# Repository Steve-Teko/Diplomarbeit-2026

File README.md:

# Diplomarbeit-2026
Offizielle Repository fuer die Diplomarbeit von Steve

**Idee:**
Die Idee ist es Leiterplatten zu designen, die in einem neuen oder bestehenden SmartHome mit einfachen Schritten integrierbar sind.
Es sollen einfache aber Funktionsreiche Leiterplatten die z.B. im Fall des Aktor Prints, per I2C an bereits vorhandene Steuerungen verwendet werden koennen.

**Meine Qualifikationen:**
Gelernt habe ich Automatiker und interessiere mich seit meiner Kindheit fuer viele Technik relevante Themen. Schulisch war ich schon immer einer dem die Themen Kunst und Sprachen weniger interessierten im vergleich zu Mathe, Physik und Handarbeit.
Mit 23 hatte ich eine Entscheidung getroffen, mich Schulisch weiterzubilden. Dies ist bis jetzt immer noch eine Entscheidung die ich nicht bereue. Der Weg bis zu dieser Arbeit war steinig und hart.
Leiterplatten hatte ich einmal in der Lehre mit meinem damaligen Lehrlingsbetreuer gezeichnet, dies aber danach nie mehr ausgefuehrt. Damals hatten wir Eagle als Programm.

**Die Umsetzung:**
Zu diesem Repo existiert noch meine Arbeit die ich Paralell dazu Schreibe. Die Idee des Repo ist es die notwendigen Daten: KiCad, Gerber Files, Gehause oder Programmzeilen fuer spaetere vorhaben zu Speichern.
Die Arbeit werde ich nicht auf das Repo hochladen.

**Haftungsausschluss:**
Ich bin weder fuer die korrekte Anwendung noch meine Fehler Verantwortlich, saemtliche Schaeden die durch alle Dateien auf diesem Repo verursacht wurden, sind alleinig dem Anwender zuzuschreiben.
Die Leiterplatten sind von keinem Pruefunternehmen abgenommen oder auf ihre Sicherheit geprueft worden. Bei Verwendung sind alle Regeln der Technik zu beachten.

#################################################################################################

Official repository for Steve's diploma thesis.

**Idea**
The concept is to design printed circuit boards (PCBs) that can be easily integrated into a new or existing smart home system.
The goal is to create simple yet feature-rich PCBs—such as the actuator board—that can connect to existing control systems via I2C.

**My Qualifications**
I am a trained automation technician (Automatiker) and have been interested in various tech-related topics since childhood. At school, I was always far less interested in art and languages compared to math, physics, and practical crafts.
At age 23, I decided to further my education—a choice I still do not regret. The path leading up to this project has been tough and challenging.
I had designed PCBs once during my apprenticeship alongside my mentor using EAGLE, but I never worked with PCB design again after that.

**Implementation**
In addition to this repository, I am writing my written thesis in parallel. The purpose of this repo is to store the necessary project files—such as KiCad files, Gerber files, enclosure models, or code lines—for future reference.
I will not be uploading the written thesis itself to this repository.

**Disclaimer**
I am responsible neither for the correct application of these files nor for any errors within them. Any damages caused by files in this repository are solely the responsibility of the user.
The PCBs have not been certified or safety-tested by any official inspection body. When using them, all applicable engineering standards and safety codes must be strictly followed.

**What to expect:**
You will be able to order a the Following PCB from your favorite PCB Manufacturer, the Files and a basic Enclosure designed in FreeCAD is included in the Folders

**Hauptprint aka the Brain**
It's purpose is being able to be integrated in to your existing SmartHome while offering a wide range off preconfigured In/Output.
The ESP32 C6 Wroom1 supports Thread/Zigbee, Wi-Fi 6 (2.4gHz only!), Bluetooth 5.0, UART, I2C and I2S.

**The RelaisExpanderPrint aka the Switchmaster**
The RelaisExpanderPrint was designed with compatibility and versatility in mind. The Idea was to create a 16x Relays Switching device with Potential-free contacts in mind, as you would find on a PLC or in an Switching Cabinet.
Its size is as compact as i was able to design it with an Power-supply input that support different Voltage Levels depending on your needs.
The TracoPower Component (PS1) is interchangeable in its product line so you can choose Supply Voltages ranging from 9V,12V,24V or up to 75V DC.

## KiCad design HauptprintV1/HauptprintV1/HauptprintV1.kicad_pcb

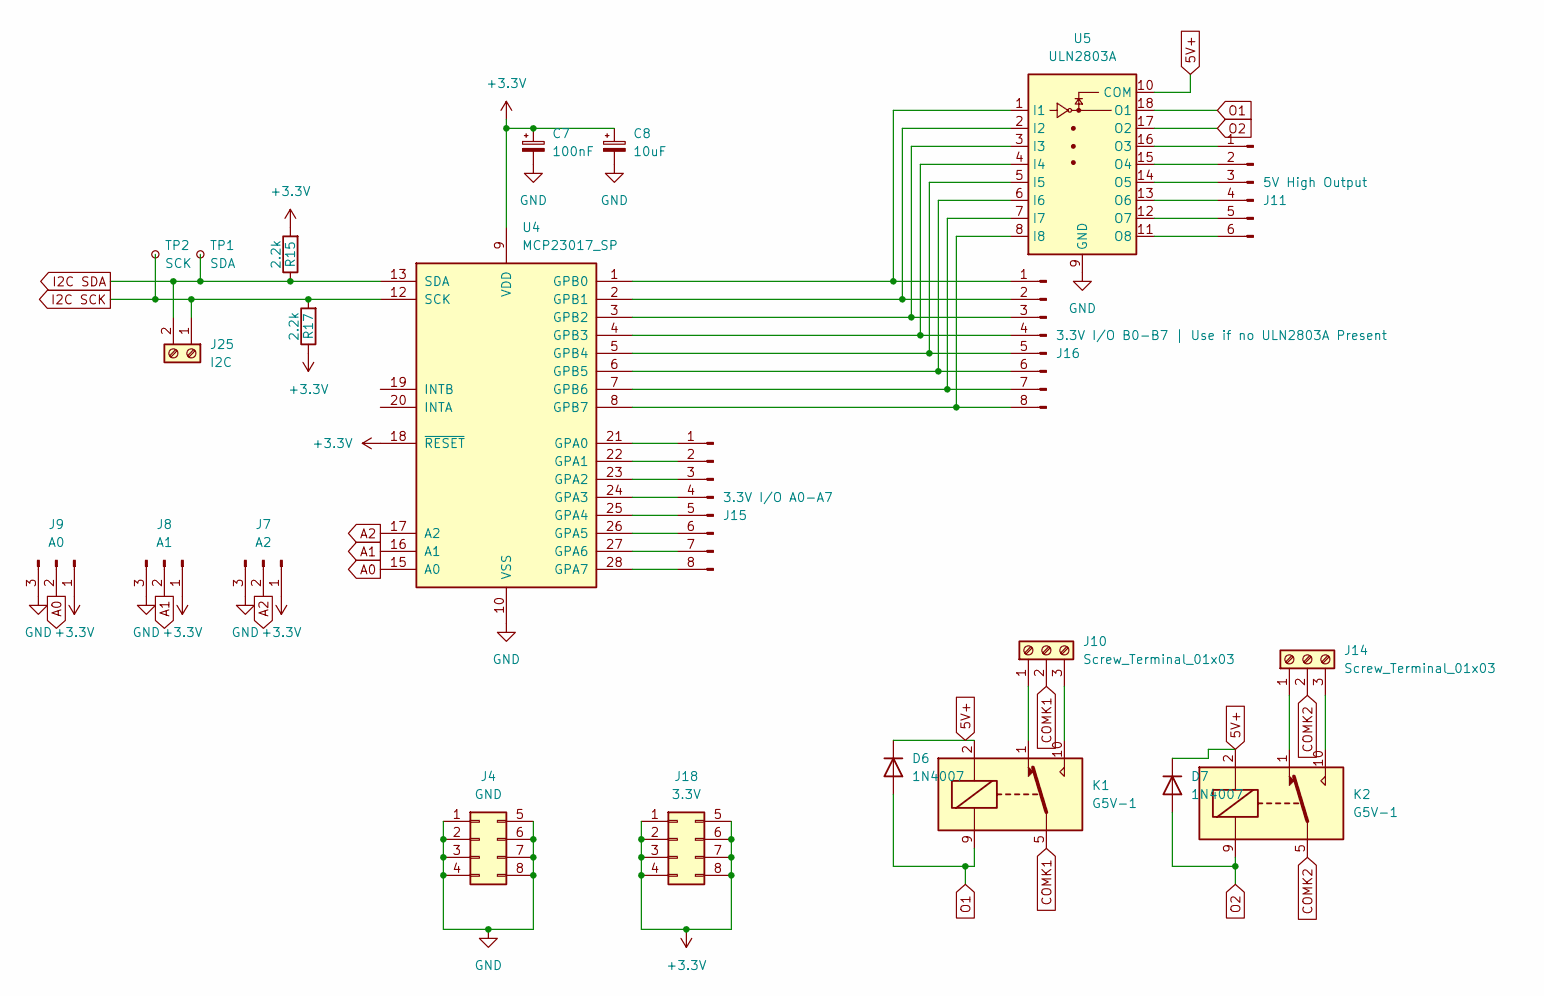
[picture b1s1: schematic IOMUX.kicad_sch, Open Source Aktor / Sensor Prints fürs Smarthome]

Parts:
C7: 100nF; CP_EIA-6032-20_AVX-F_HandSolder
C8: 10uF; CP_Radial_D4.0mm_P1.50mm
D6, D7: 1N4007; D_DO-41_SOD81_P10.16mm_Horizontal
J4: GND; PinSocket_2x04_P2.54mm_Vertical
J7: A2; PinHeader_1x03_P2.54mm_Vertical
J8: A1; PinHeader_1x03_P2.54mm_Vertical
J9: A0; PinHeader_1x03_P2.54mm_Vertical
J10, J14: Screw_Terminal_01x03; TerminalBlock_Phoenix_MPT-0,5-3-2.54_1x03_P2.54mm_Horizontal
J11: 5V High Output; PinHeader_1x06_P2.54mm_Vertical
J15: 3.3V I/O A0-A7; PinHeader_1x08_P2.54mm_Vertical
J16: 3.3V I/O B0-B7 | Use if no ULN2803A Present; PinHeader_1x08_P2.54mm_Vertical
J18: 3.3V; PinSocket_2x04_P2.54mm_Vertical
J25: I2C; TerminalBlock_Phoenix_MPT-0,5-2-2.54_1x02_P2.54mm_Horizontal
K1, K2: G5V-1; Relay_SPDT_Omron_G5V-1
R15, R17: 2.2k; R_1206_3216Metric_Pad1.30x1.75mm_HandSolder
TP1: SDA; TestPoint_Pad_D2.0mm
TP2: SCK; TestPoint_Pad_D2.0mm
U4: MCP23017_SP; DIP-28_W7.62mm
U5: ULN2803A; DIP-18_W7.62mm

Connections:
3.3V: C7.1, C8.1, J7.1, J8.1, J9.1, J18.1, J18.2, J18.3, J18.4, J18.5, J18.6, J18.7, J18.8, R15.2, R17.1, U4.9 (VDD), U4.18 (~RESET); also elsewhere on the board
5V+: D6.1 (K), D7.1 (K), K1.2, K2.2, U5.10 (COM); also elsewhere on the board
A0: J9.2, U4.15 (A0)
A1: J8.2, U4.16 (A1)
A2: J7.2, U4.17 (A2)
COMK1: J10.2, K1.5, K1.6
COMK2: J14.2, K2.5, K2.6
GND: C7.2, C8.2, J4.1, J4.2, J4.3, J4.4, J4.5, J4.6, J4.7, J4.8, J7.3, J8.3, J9.3, U4.10 (VSS), U5.9 (GND); also elsewhere on the board
I2C SCK: J25.1, R17.2, TP2.1 (1_1), U4.12 (SCK); also elsewhere on the board
I2C SDA: J25.2, R15.1, TP1.1 (1_1), U4.13 (SDA); also elsewhere on the board
unnamed: J10.1, K1.1
unnamed: J10.3, K1.10
unnamed: J11.1, U5.16 (O3)
unnamed: J11.2, U5.15 (O4)
unnamed: J11.3, U5.14 (O5)
unnamed: J11.4, U5.13 (O6)
unnamed: J11.5, U5.12 (O7)
unnamed: J11.6, U5.11 (O8)
unnamed: J14.1, K2.1
unnamed: J14.3, K2.10
unnamed: J15.1, U4.21 (GPA0)
unnamed: J15.2, U4.22 (GPA1)
unnamed: J15.3, U4.23 (GPA2)
unnamed: J15.4, U4.24 (GPA3)
unnamed: J15.5, U4.25 (GPA4)
unnamed: J15.6, U4.26 (GPA5)
unnamed: J15.7, U4.27 (GPA6)
unnamed: J15.8, U4.28 (GPA7)
unnamed: J16.1, U4.1 (GPB0), U5.1 (I1)
unnamed: J16.2, U4.2 (GPB1), U5.2 (I2)
unnamed: J16.3, U4.3 (GPB2), U5.3 (I3)
unnamed: J16.4, U4.4 (GPB3), U5.4 (I4)
unnamed: J16.5, U4.5 (GPB4), U5.5 (I5)
unnamed: J16.6, U4.6 (GPB5), U5.6 (I6)
unnamed: J16.7, U4.7 (GPB6), U5.7 (I7)
unnamed: J16.8, U4.8 (GPB7), U5.8 (I8)
O1: D6.2 (A), K1.9, U5.18 (O1)
O2: D7.2 (A), K2.9, U5.17 (O2)

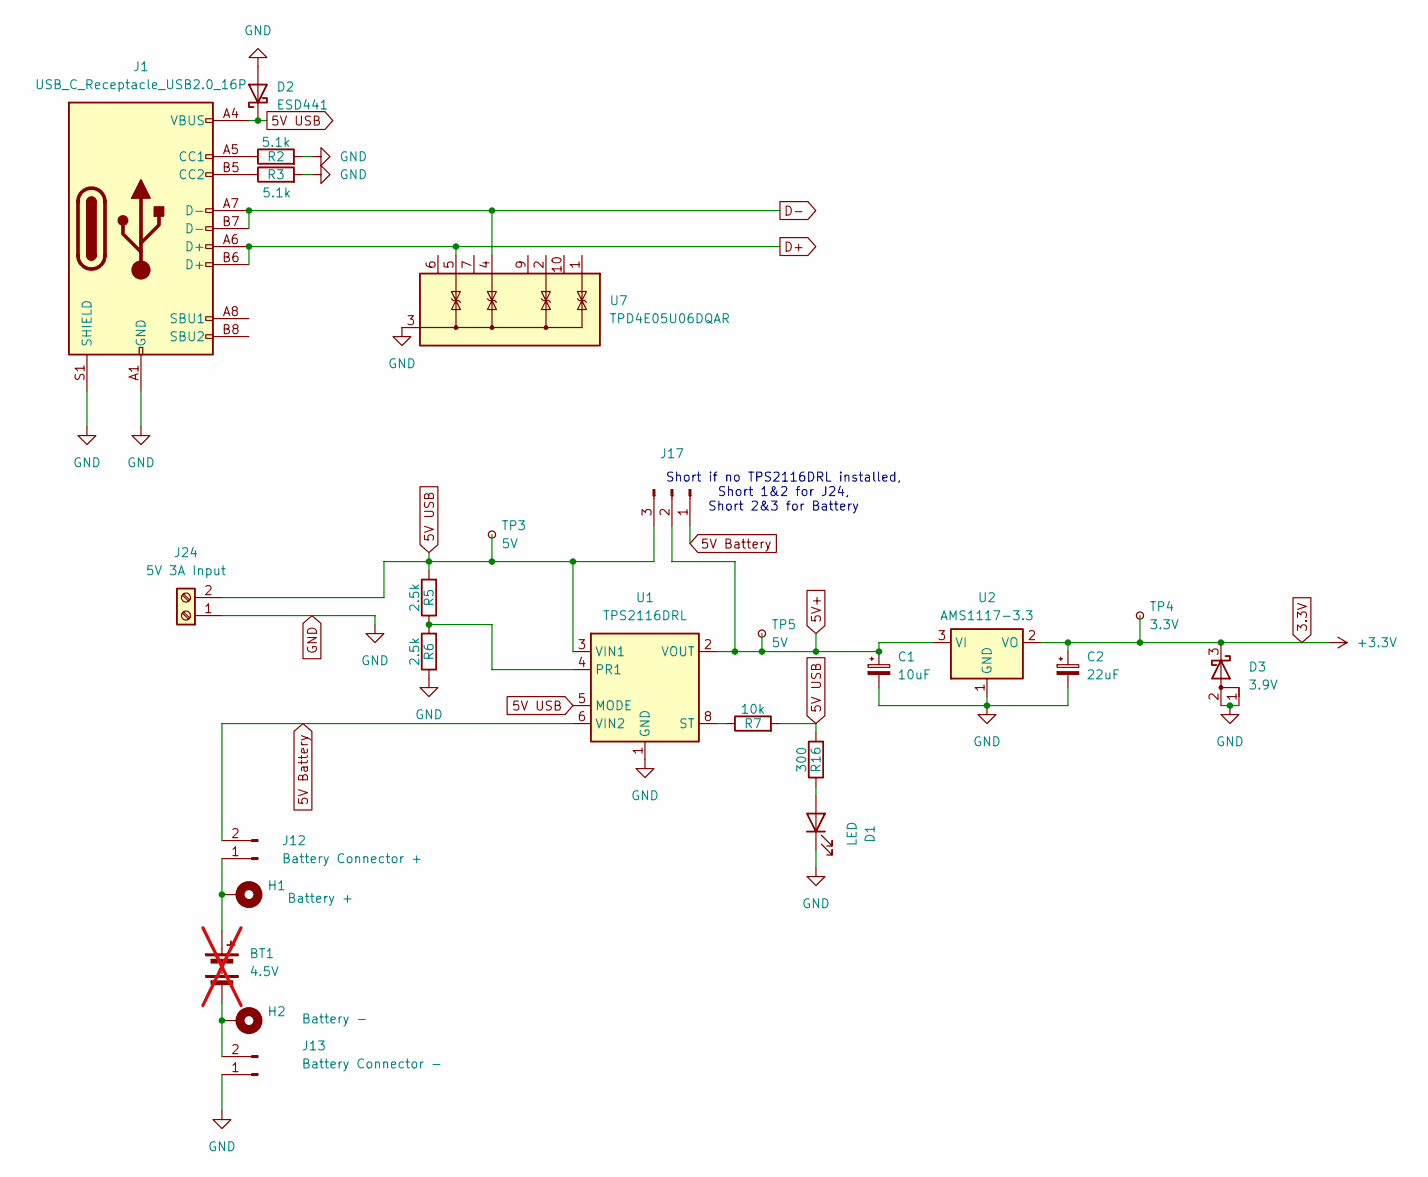
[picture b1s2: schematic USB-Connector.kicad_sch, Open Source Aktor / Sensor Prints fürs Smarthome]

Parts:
BT1: 4.5V; not fitted
C1: 10uF; CP_EIA-6032-20_AVX-F_HandSolder
C2: 22uF; CP_EIA-6032-20_AVX-F_HandSolder
D1: LED; LED_D3.0mm_Clear
D2: ESD441; D_0603_1608Metric
D3: 3.9V; TSOT-23
H1: Battery +; MountingHole_2.2mm_M2_DIN965_Pad
H2: Battery -; MountingHole_2.2mm_M2_DIN965_Pad
J1: USB_C_Receptacle_USB2.0_16P; USB_C_Receptacle_GCT_USB4085
J12: Battery Connector +; PinHeader_1x02_P2.54mm_Vertical
J13: Battery Connector -; PinHeader_1x02_P2.54mm_Vertical
J17: PinHeader_1x03_P2.54mm_Vertical
J24: 5V 3A Input; TerminalBlock_Phoenix_MPT-0,5-2-2.54_1x02_P2.54mm_Horizontal
R2, R3: 5.1k; R_1206_3216Metric_Pad1.30x1.75mm_HandSolder
R5, R6: 2.5k; R_1206_3216Metric_Pad1.30x1.75mm_HandSolder
R7: 10k; R_1206_3216Metric_Pad1.30x1.75mm_HandSolder
R16: 300; R_Axial_DIN0207_L6.3mm_D2.5mm_P10.16mm_Horizontal
TP3, TP5: 5V; TestPoint_Pad_D2.0mm
TP4: 3.3V; TestPoint_Pad_D2.0mm
U1: TPS2116DRL; SOT-583-8
U2: AMS1117-3.3; SOT-223-3_TabPin2
U7: TPD4E05U06DQAR; USON-10_2.5x1.0mm_P0.5mm

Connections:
3.3V: C2.1, D3.3 (K), TP4.1 (1_1), U2.2 (VO); also elsewhere on the board
5V Battery: J12.2, J17.1, U1.6 (VIN2)
5V USB: D2.1 (K), J1.A4 (VBUS), J1.A9 (VBUS), J1.B4 (VBUS), J1.B9 (VBUS), J17.3, J24.2, R5.2, R7.2, R16.2, TP3.1 (1_1), U1.3 (VIN1), U1.5 (MODE)
5V+: C1.1, J17.2, TP5.1 (1_1), U1.2 (VOUT), U1.7 (VOUT), U2.3 (VI); also elsewhere on the board
D+: J1.A6 (D+), J1.B6 (D+), U7.5 (IO4); also elsewhere on the board
D-: J1.A7 (D-), J1.B7 (D-), U7.4 (IO3); also elsewhere on the board
GND: C1.2, C2.2, D1.1 (K), D2.2 (A), D3.1 (A), D3.2 (A), J1.A1 (GND), J1.A12 (GND), J1.B1 (GND), J1.B12 (GND), J1.S1 (SHIELD), J13.1, J24.1, R2.2, R3.2, R6.1, U1.1 (GND), U2.1 (GND), U7.3 (G), U7.8 (G); also elsewhere on the board
unnamed: D1.2 (A), R16.1
unnamed: J1.A5 (CC1), R2.1
unnamed: J1.B5 (CC2), R3.1
unnamed: BT1.1 (+), H1.1 (1_1), J12.1
unnamed: BT1.2 (-), H2.1 (1_1), J13.2
unnamed: R5.1, R6.2, U1.4 (PR1)
unnamed: R7.1, U1.8 (ST)

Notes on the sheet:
Short if no TPS2116DRL installed, Short 1&2 for J24, Short 2&3 for Battery

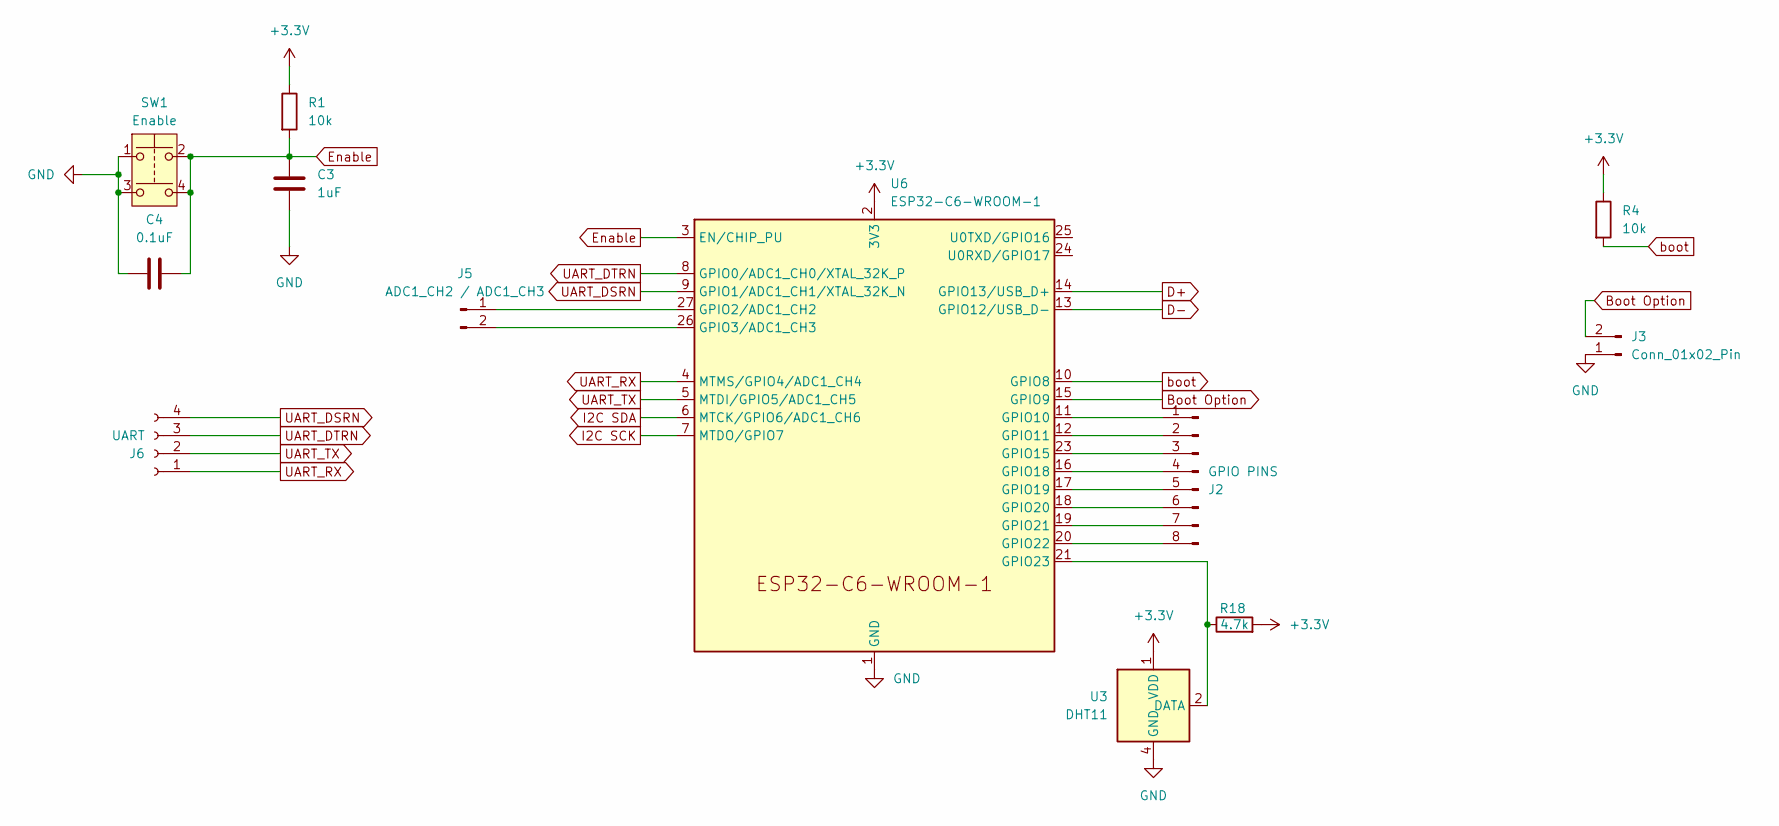
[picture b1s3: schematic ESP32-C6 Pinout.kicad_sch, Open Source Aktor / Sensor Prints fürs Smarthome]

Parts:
C3: 1uF; C_1210_3225Metric_Pad1.33x2.70mm_HandSolder
C4: 0.1uF; C_1210_3225Metric_Pad1.33x2.70mm_HandSolder
J2: GPIO PINS; PinHeader_1x08_P2.54mm_Vertical
J3: Conn_01x02_Pin; PinHeader_1x02_P2.54mm_Vertical
J5: ADC1_CH2 / ADC1_CH3; PinHeader_1x02_P2.54mm_Vertical
J6: UART; PinHeader_1x04_P2.54mm_Vertical
R1, R4: 10k; R_1206_3216Metric_Pad1.30x1.75mm_HandSolder
R18: 4.7k; R_Axial_DIN0207_L6.3mm_D2.5mm_P10.16mm_Horizontal
SW1: Enable; SW_PUSH_6mm
U3: DHT11; Aosong_DHT11_5.5x12.0_P2.54mm
U6: ESP32-C6-WROOM-1

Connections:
3.3V: R1.1, R4.1, R18.2, U3.1 (VDD), U6.2 (3V3); also elsewhere on the board
Boot Option: J3.2, U6.15 (GPIO9)
D+: U6.14 (GPIO13/USB_D+); also elsewhere on the board
D-: U6.13 (GPIO12/USB_D-); also elsewhere on the board
Enable: C3.1, C4.2, R1.2, SW1.2, SW1.4, U6.3 (EN/CHIP_PU)
GND: C3.2, C4.1, J3.1, SW1.1, SW1.3, U3.4 (GND), U6.1 (GND), U6.28 (GND), U6.29 (GND); also elsewhere on the board
I2C SCK: U6.7 (MTDO/GPIO7); also elsewhere on the board
I2C SDA: U6.6 (MTCK/GPIO6/ADC1_CH6); also elsewhere on the board
unnamed: J2.1, U6.11 (GPIO10)
unnamed: J2.2, U6.12 (GPIO11)
unnamed: J2.3, U6.23 (GPIO15)
unnamed: J2.4, U6.16 (GPIO18)
unnamed: J2.5, U6.17 (GPIO19)
unnamed: J2.6, U6.18 (GPIO20)
unnamed: J2.7, U6.19 (GPIO21)
unnamed: J2.8, U6.20 (GPIO22)
unnamed: J5.1, U6.27 (GPIO2/ADC1_CH2)
unnamed: J5.2, U6.26 (GPIO3/ADC1_CH3)
unnamed: R18.1, U3.2 (DATA), U6.21 (GPIO23)
UART_DSRN: J6.4, U6.9 (GPIO1/ADC1_CH1/XTAL_32K_N)
UART_DTRN: J6.3, U6.8 (GPIO0/ADC1_CH0/XTAL_32K_P)
UART_RX: J6.1, U6.4 (MTMS/GPIO4/ADC1_CH4)
UART_TX: J6.2, U6.5 (MTDI/GPIO5/ADC1_CH5)
boot: R4.2, U6.10 (GPIO8)

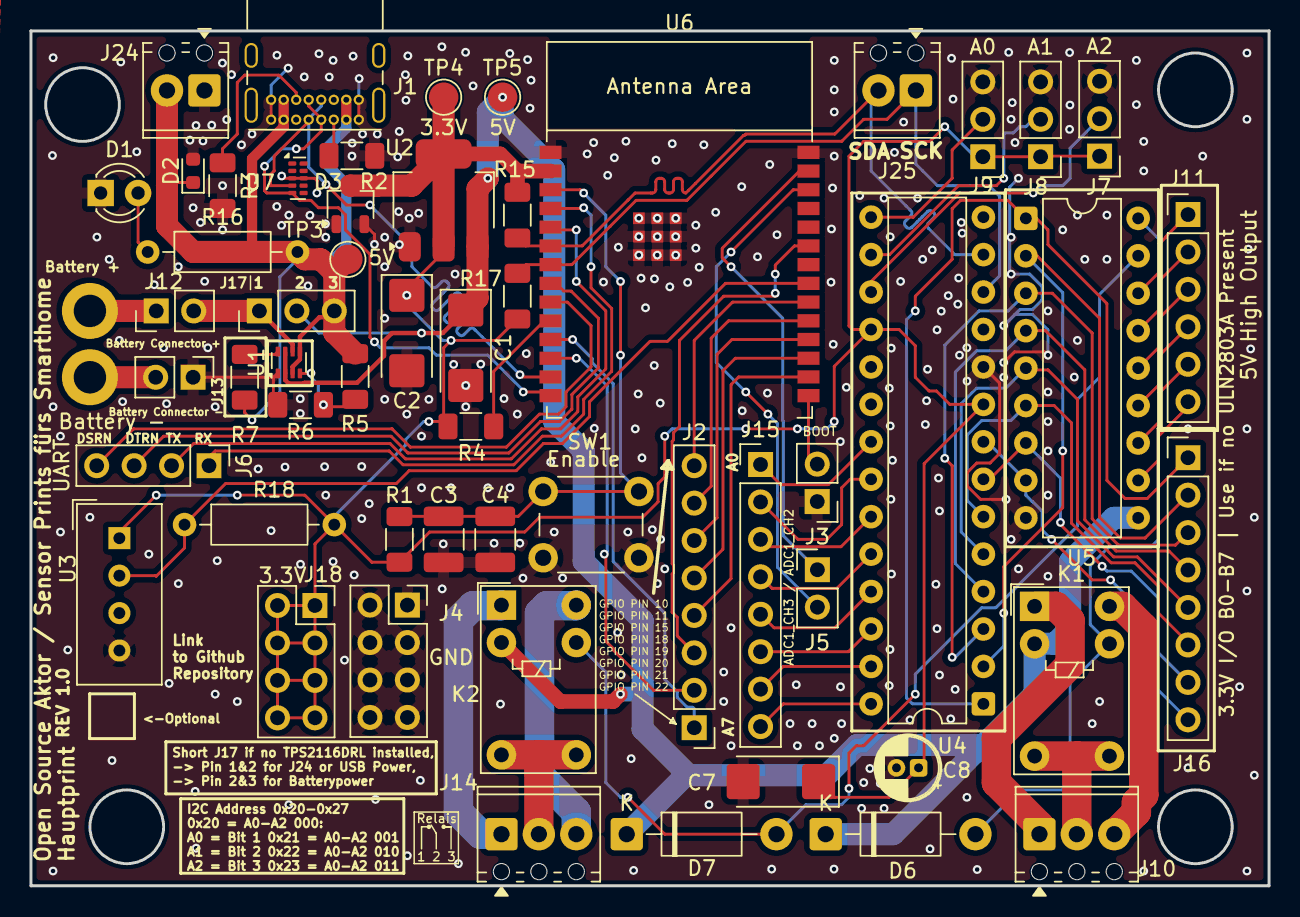
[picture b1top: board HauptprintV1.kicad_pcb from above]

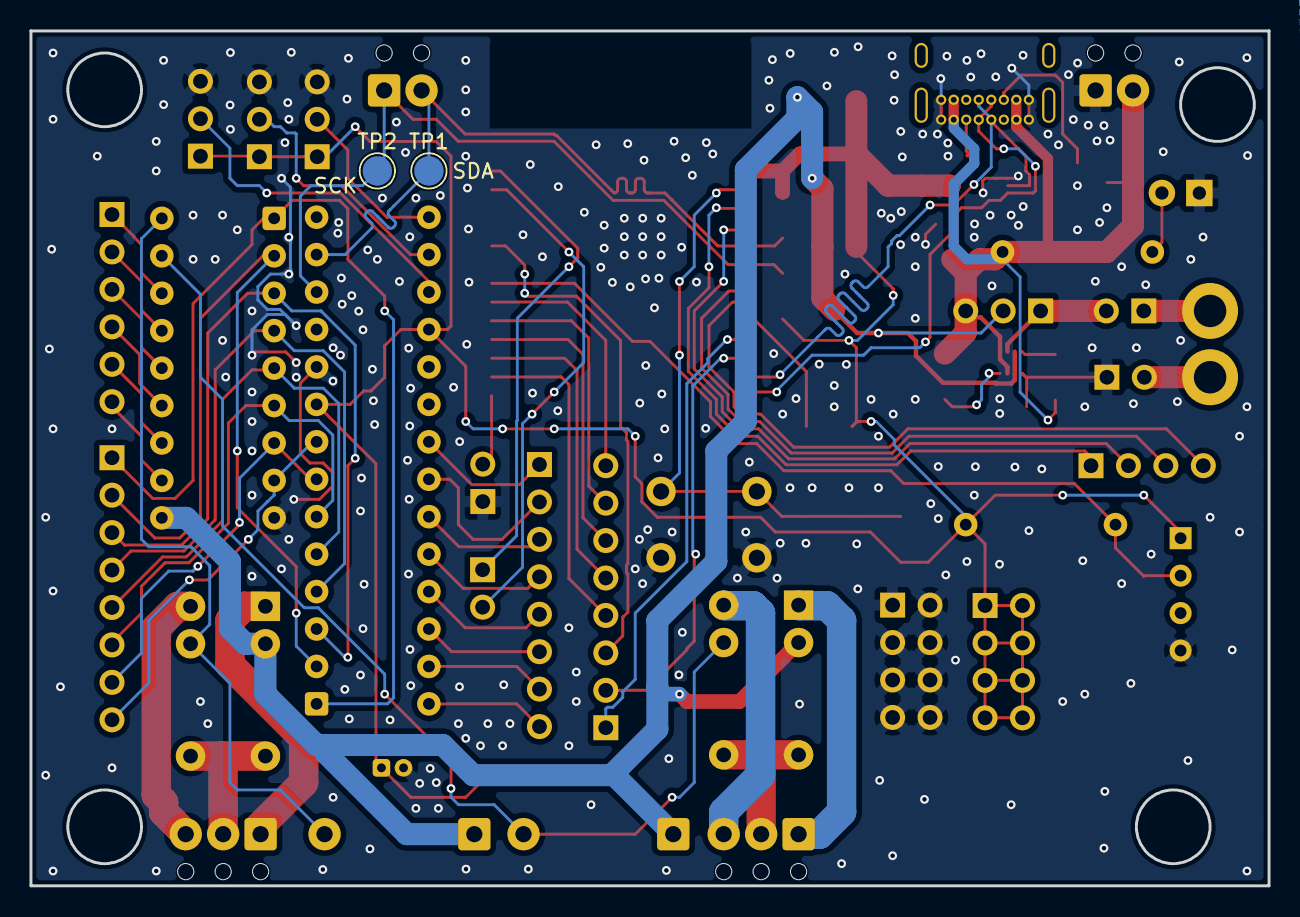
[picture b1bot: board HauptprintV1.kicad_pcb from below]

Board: 2 copper layers, 84.0 x 58.0 mm, 59 parts (2 on the bottom side), 67 nets.

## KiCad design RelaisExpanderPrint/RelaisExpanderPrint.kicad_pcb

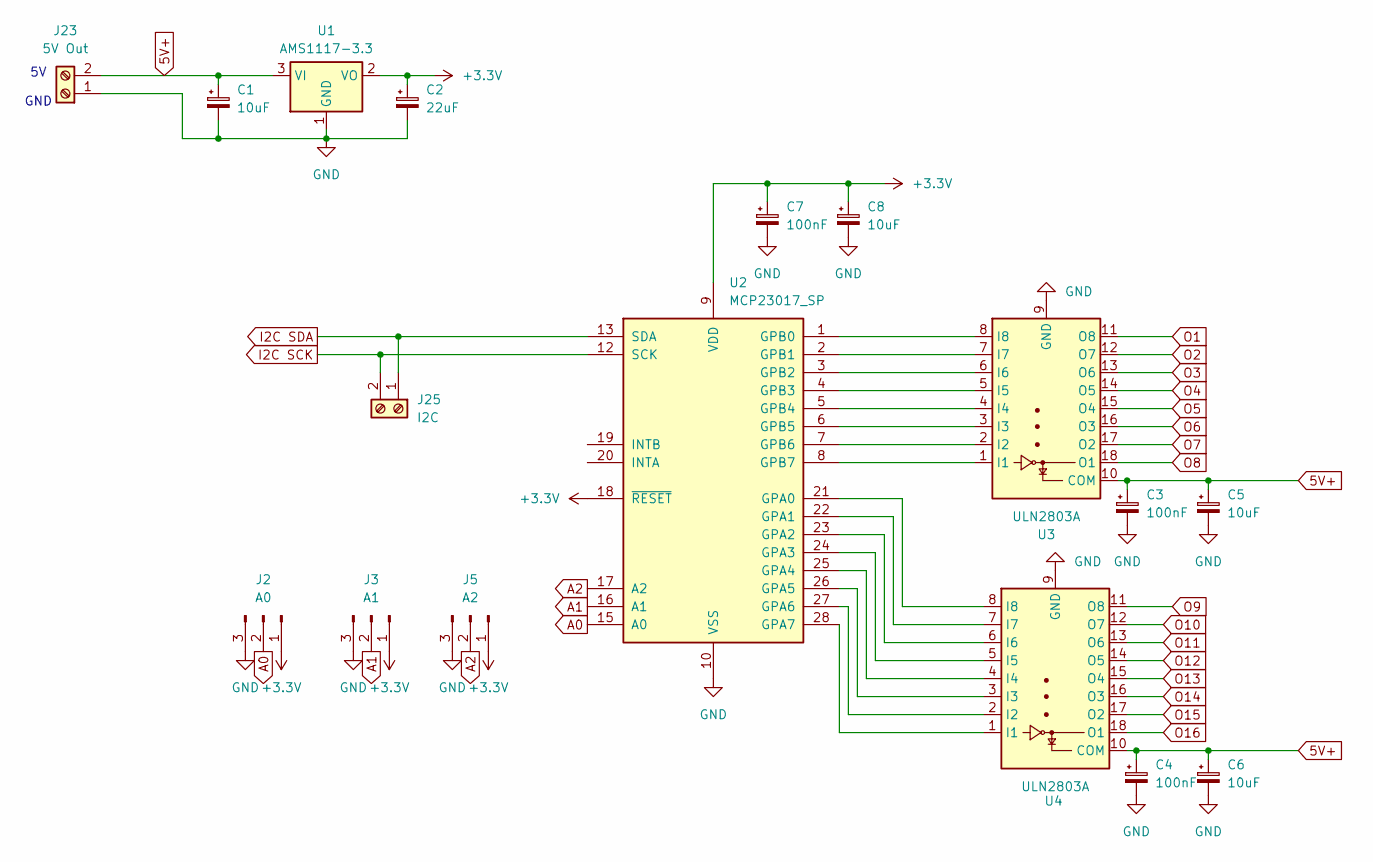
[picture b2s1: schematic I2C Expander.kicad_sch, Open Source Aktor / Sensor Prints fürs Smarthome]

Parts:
C1, C5, C6, C8: 10uF; CP_EIA-6032-20_AVX-F_HandSolder
C2: 22uF; CP_EIA-6032-20_AVX-F_HandSolder
C3, C4, C7: 100nF; CP_EIA-6032-20_AVX-F_HandSolder
J2: A0; PinHeader_1x03_P2.54mm_Vertical
J3: A1; PinHeader_1x03_P2.54mm_Vertical
J5: A2; PinHeader_1x03_P2.54mm_Vertical
J23: 5V Out; TerminalBlock_Phoenix_MPT-0,5-2-2.54_1x02_P2.54mm_Horizontal
J25: I2C; TerminalBlock_Phoenix_MPT-0,5-2-2.54_1x02_P2.54mm_Horizontal
U1: AMS1117-3.3; SOT-223-3_TabPin2
U2: MCP23017_SP; DIP-28_W7.62mm
U3, U4: ULN2803A; DIP-18_W7.62mm

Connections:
5V+: C1.1, C3.1, C4.1, C5.1, C6.1, J23.2, U1.3 (VI), U3.10 (COM), U4.10 (COM); also elsewhere on the board
+3.3V: C2.1, C7.1, C8.1, J2.1, J3.1, J5.1, U1.2 (VO), U2.9 (VDD), U2.18 (~RESET)
A0: J2.2, U2.15 (A0)
A1: J3.2, U2.16 (A1)
A2: J5.2, U2.17 (A2)
GND: C1.2, C2.2, C3.2, C4.2, C5.2, C6.2, C7.2, C8.2, J2.3, J3.3, J5.3, J23.1, U1.1 (GND), U2.10 (VSS), U3.9 (GND), U4.9 (GND); also elsewhere on the board
I2C +: J25.1, U2.13 (SDA)
I2C -: J25.2, U2.12 (SCK)
unnamed: U2.21 (GPA0), U4.8 (I8)
unnamed: U2.22 (GPA1), U4.7 (I7)
unnamed: U2.23 (GPA2), U4.6 (I6)
unnamed: U2.24 (GPA3), U4.5 (I5)
unnamed: U2.25 (GPA4), U4.4 (I4)
unnamed: U2.26 (GPA5), U4.3 (I3)
unnamed: U2.27 (GPA6), U4.2 (I2)
unnamed: U2.28 (GPA7), U4.1 (I1)
unnamed: U2.1 (GPB0), U3.8 (I8)
unnamed: U2.2 (GPB1), U3.7 (I7)
unnamed: U2.3 (GPB2), U3.6 (I6)
unnamed: U2.4 (GPB3), U3.5 (I5)
unnamed: U2.5 (GPB4), U3.4 (I4)
unnamed: U2.6 (GPB5), U3.3 (I3)
unnamed: U2.7 (GPB6), U3.2 (I2)
unnamed: U2.8 (GPB7), U3.1 (I1)
O1: U3.11 (O8); also elsewhere on the board
O2: U3.12 (O7); also elsewhere on the board
O3: U3.13 (O6); also elsewhere on the board
O4: U3.14 (O5); also elsewhere on the board
O5: U3.15 (O4); also elsewhere on the board
O6: U3.16 (O3); also elsewhere on the board
O7: U3.17 (O2); also elsewhere on the board
O8: U3.18 (O1); also elsewhere on the board
O9: U4.11 (O8); also elsewhere on the board
O10: U4.12 (O7); also elsewhere on the board
O11: U4.13 (O6); also elsewhere on the board
O12: U4.14 (O5); also elsewhere on the board
O13: U4.15 (O4); also elsewhere on the board
O14: U4.16 (O3); also elsewhere on the board
O15: U4.17 (O2); also elsewhere on the board
O16: U4.18 (O1); also elsewhere on the board

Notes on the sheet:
5V GND

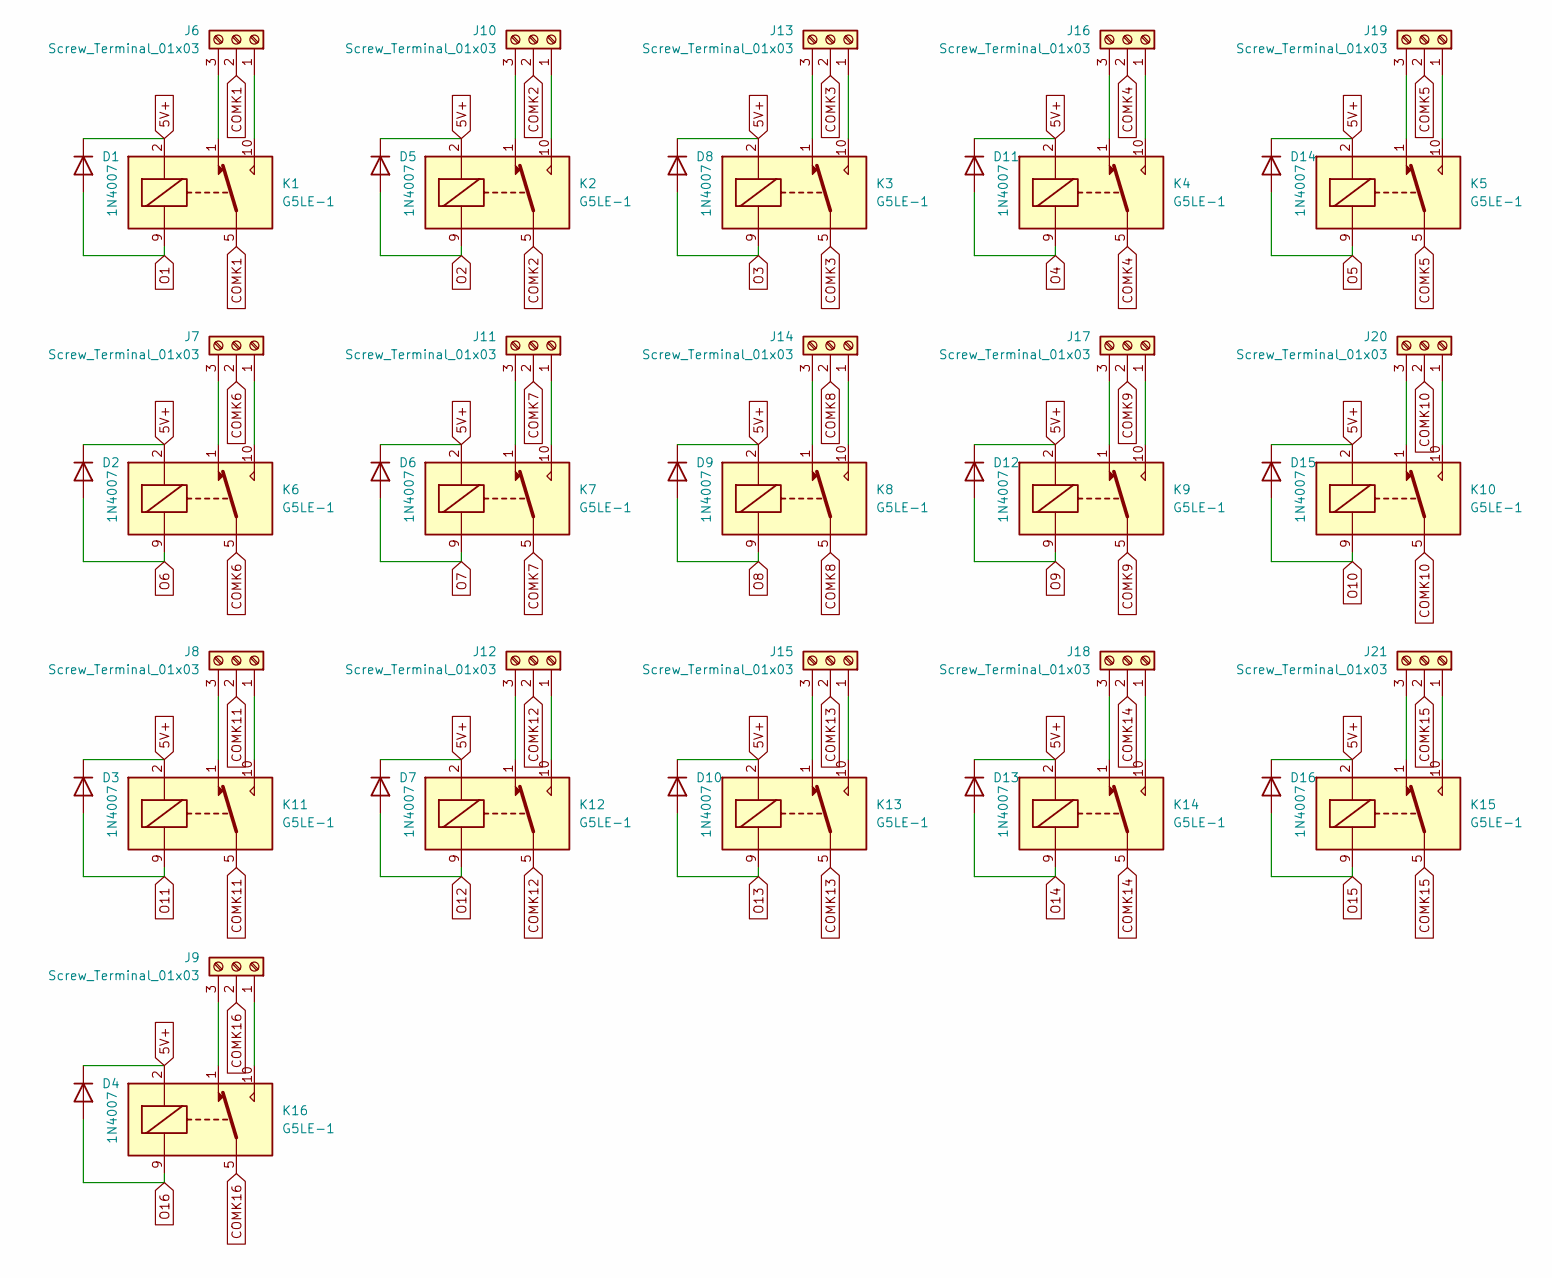
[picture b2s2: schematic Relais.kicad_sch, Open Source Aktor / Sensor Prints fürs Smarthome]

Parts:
D1, D2, D3, D4, D5, D6, D7, D8, D9, D10, D11, D12, D13, D14, D15, D16: 1N4007; D_DO-41_SOD81_P10.16mm_Horizontal
J6, J7, J8, J9, J10, J11, J12, J13, J14, J15, J16, J17, J18, J19, J20, J21: Screw_Terminal_01x03; TerminalBlock_Phoenix_MPT-0,5-3-2.54_1x03_P2.54mm_Horizontal
K1, K2, K3, K4, K5, K6, K7, K8, K9, K10, K11, K12, K13, K14, K15, K16: G5LE-1; Relay_SPDT_Omron_G5V-1

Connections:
5V+: D1.1 (K), D2.1 (K), D3.1 (K), D4.1 (K), D5.1 (K), D6.1 (K), D7.1 (K), D8.1 (K), D9.1 (K), D10.1 (K), D11.1 (K), D12.1 (K), D13.1 (K), D14.1 (K), D15.1 (K), D16.1 (K), K1.2, K2.2, K3.2, K4.2, K5.2, K6.2, K7.2, K8.2, K9.2, K10.2, K11.2, K12.2, K13.2, K14.2, K15.2, K16.2; also elsewhere on the board
COMK1: J6.2, K1.5, K1.6
COMK2: J10.2, K2.5, K2.6
COMK3: J13.2, K3.5, K3.6
COMK4: J16.2, K4.5, K4.6
COMK5: J19.2, K5.5, K5.6
COMK6: J7.2, K6.5, K6.6
COMK7: J11.2, K7.5, K7.6
COMK8: J14.2, K8.5, K8.6
COMK9: J17.2, K9.5, K9.6
COMK10: J20.2, K10.5, K10.6
COMK11: J8.2, K11.5, K11.6
COMK12: J12.2, K12.5, K12.6
COMK13: J15.2, K13.5, K13.6
COMK14: J18.2, K14.5, K14.6
COMK15: J21.2, K15.5, K15.6
COMK16: J9.2, K16.5, K16.6
unnamed: J6.1, K1.10
unnamed: J6.3, K1.1
unnamed: J7.1, K6.10
unnamed: J7.3, K6.1
unnamed: J8.1, K11.10
unnamed: J8.3, K11.1
unnamed: J9.1, K16.10
unnamed: J9.3, K16.1
unnamed: J10.1, K2.10
unnamed: J10.3, K2.1
unnamed: J11.1, K7.10
unnamed: J11.3, K7.1
unnamed: J12.1, K12.10
unnamed: J12.3, K12.1
unnamed: J13.1, K3.10
unnamed: J13.3, K3.1
unnamed: J14.1, K8.10
unnamed: J14.3, K8.1
unnamed: J15.1, K13.10
unnamed: J15.3, K13.1
unnamed: J16.1, K4.10
unnamed: J16.3, K4.1
unnamed: J17.1, K9.10
unnamed: J17.3, K9.1
unnamed: J18.1, K14.10
unnamed: J18.3, K14.1
unnamed: J19.1, K5.10
unnamed: J19.3, K5.1
unnamed: J20.1, K10.10
unnamed: J20.3, K10.1
unnamed: J21.1, K15.10
unnamed: J21.3, K15.1
O1: D1.2 (A), K1.9; also elsewhere on the board
O2: D5.2 (A), K2.9; also elsewhere on the board
O3: D8.2 (A), K3.9; also elsewhere on the board
O4: D11.2 (A), K4.9; also elsewhere on the board
O5: D14.2 (A), K5.9; also elsewhere on the board
O6: D2.2 (A), K6.9; also elsewhere on the board
O7: D6.2 (A), K7.9; also elsewhere on the board
O8: D9.2 (A), K8.9; also elsewhere on the board
O9: D12.2 (A), K9.9; also elsewhere on the board
O10: D15.2 (A), K10.9; also elsewhere on the board
O11: D3.2 (A), K11.9; also elsewhere on the board
O12: D7.2 (A), K12.9; also elsewhere on the board
O13: D10.2 (A), K13.9; also elsewhere on the board
O14: D13.2 (A), K14.9; also elsewhere on the board
O15: D16.2 (A), K15.9; also elsewhere on the board
O16: D4.2 (A), K16.9; also elsewhere on the board

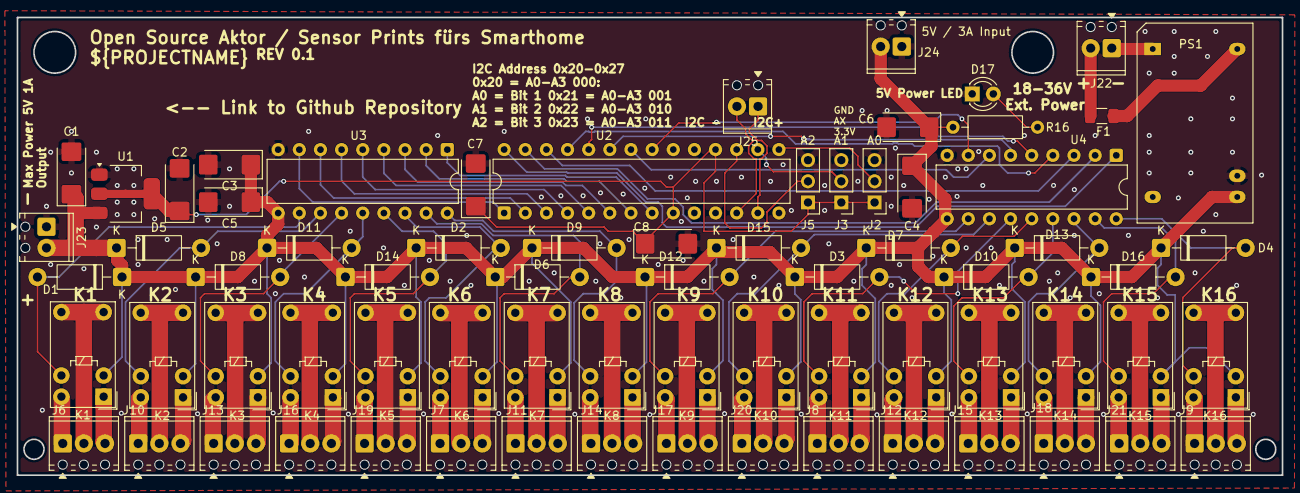
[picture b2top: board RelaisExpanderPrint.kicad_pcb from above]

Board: 2 copper layers, 152.0 x 55.0 mm, 71 parts (0 on the bottom side), 92 nets.

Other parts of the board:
D17: LED; LED_D3.0mm_Clear
F1: Fuse; Fuse_1206_3216Metric
J22: 18-36V External Powersupply; TerminalBlock_Phoenix_MPT-0,5-2-2.54_1x02_P2.54mm_Horizontal
J24: 5V / 3A Input; TerminalBlock_Phoenix_MPT-0,5-2-2.54_1x02_P2.54mm_Horizontal
PS1: TEL_15-2411N; Converter_DCDC_TRACO_TEL12-xxxx_THT
R16: 300; R_Axial_DIN0207_L6.3mm_D2.5mm_P10.16mm_Horizontal

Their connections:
5V+: J24.2, PS1.9 (+VOUT), R16.2; also elsewhere on the board
GND: D17.1 (K), J24.1, PS1.10 (-VOUT); also elsewhere on the board
unnamed: D17.2 (A), R16.1
unnamed: J22.1, PS1.1 (-VIN)
unnamed: F1.1, J22.2
unnamed: F1.2, PS1.16 (+VIN)

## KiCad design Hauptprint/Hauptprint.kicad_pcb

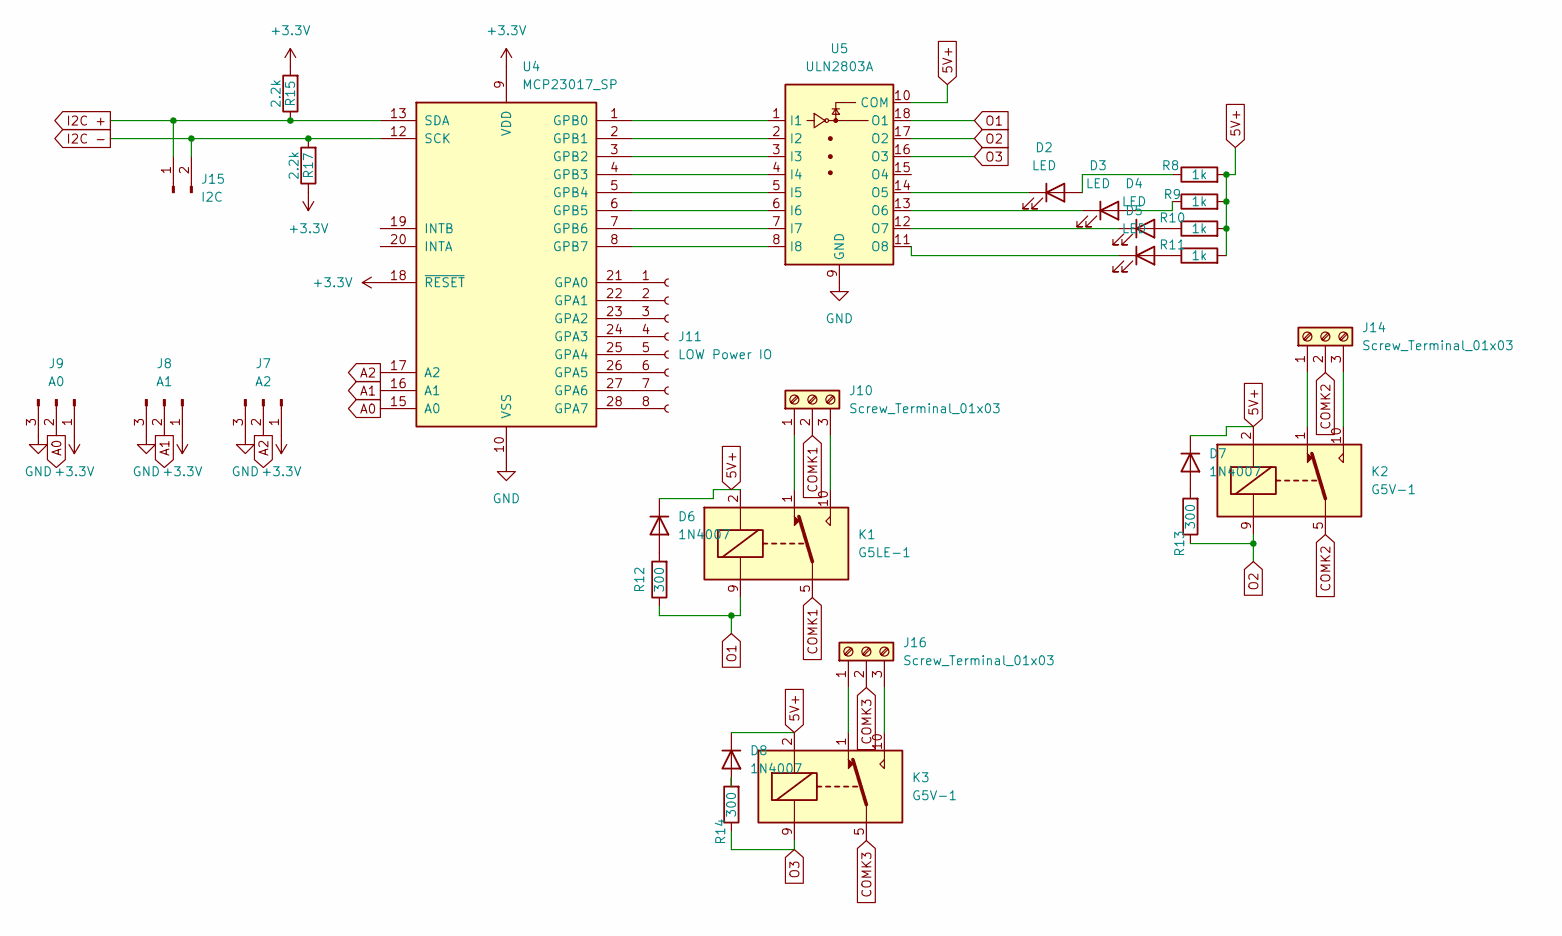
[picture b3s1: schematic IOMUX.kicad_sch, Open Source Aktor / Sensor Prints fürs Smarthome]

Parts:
D2, D3, D4, D5: LED; LED_D3.0mm
D6, D7, D8: 1N4007; D_DO-41_SOD81_P10.16mm_Horizontal
J7: A2; PinHeader_1x03_P2.54mm_Vertical
J8: A1; PinHeader_1x03_P2.54mm_Vertical
J9: A0; PinHeader_1x03_P2.54mm_Vertical
J10, J14, J16: Screw_Terminal_01x03; TerminalBlock_TE_282834-3_1x03_P2.54mm_Horizontal
J11: LOW Power IO; PinHeader_1x08_P2.54mm_Vertical
J15: I2C; PinHeader_1x02_P2.54mm_Vertical
K1: G5LE-1; Relay_SPDT_Omron_G5V-1
K2, K3: G5V-1; Relay_SPDT_Omron_G5V-1
R8, R9, R10, R11: 1k; R_Axial_DIN0207_L6.3mm_D2.5mm_P10.16mm_Horizontal
R12, R13, R14: 300; R_Axial_DIN0207_L6.3mm_D2.5mm_P10.16mm_Horizontal
R15, R17: 2.2k; R_1206_3216Metric_Pad1.30x1.75mm_HandSolder
U4: MCP23017_SP; DIP-28_W7.62mm
U5: ULN2803A; DIP-18_W7.62mm

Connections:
5V+: D6.1 (K), D7.1 (K), D8.1 (K), K1.2, K2.2, K3.2, R8.2, R9.2, R10.2, R11.2, U5.10 (COM); also elsewhere on the board
+3.3V: J7.1, J8.1, J9.1, R15.2, R17.1, U4.9 (VDD), U4.18 (~RESET); also elsewhere on the board
A0: J9.2, U4.15 (A0)
A1: J8.2, U4.16 (A1)
A2: J7.2, U4.17 (A2)
COMK1: J10.2, K1.5, K1.6
COMK2: J14.2, K2.5, K2.6
COMK3: J16.2, K3.5, K3.6
GND: J7.3, J8.3, J9.3, U4.10 (VSS), U5.9 (GND); also elsewhere on the board
I2C +: J15.1, R15.1, U4.13 (SDA); also elsewhere on the board
I2C -: J15.2, R17.2, U4.12 (SCK); also elsewhere on the board
unnamed: D2.2 (A), R8.1
unnamed: D2.1 (K), U5.14 (O5)
unnamed: D3.2 (A), R9.1
unnamed: D3.1 (K), U5.13 (O6)
unnamed: D4.2 (A), R10.1
unnamed: D4.1 (K), U5.12 (O7)
unnamed: D5.2 (A), R11.1
unnamed: D5.1 (K), U5.11 (O8)
unnamed: D6.2 (A), R12.2
unnamed: D7.2 (A), R13.2
unnamed: D8.2 (A), R14.2
unnamed: J10.1, K1.1
unnamed: J10.3, K1.10
unnamed: J11.1, U4.21 (GPA0)
unnamed: J11.2, U4.22 (GPA1)
unnamed: J11.3, U4.23 (GPA2)
unnamed: J11.4, U4.24 (GPA3)
unnamed: J11.5, U4.25 (GPA4)
unnamed: J11.6, U4.26 (GPA5)
unnamed: J11.7, U4.27 (GPA6)
unnamed: J11.8, U4.28 (GPA7)
unnamed: J14.1, K2.1
unnamed: J14.3, K2.10
unnamed: J16.1, K3.1
unnamed: J16.3, K3.10
unnamed: U4.1 (GPB0), U5.1 (I1)
unnamed: U4.2 (GPB1), U5.2 (I2)
unnamed: U4.3 (GPB2), U5.3 (I3)
unnamed: U4.4 (GPB3), U5.4 (I4)
unnamed: U4.5 (GPB4), U5.5 (I5)
unnamed: U4.6 (GPB5), U5.6 (I6)
unnamed: U4.7 (GPB6), U5.7 (I7)
unnamed: U4.8 (GPB7), U5.8 (I8)
O1: K1.9, R12.1, U5.18 (O1)
O2: K2.9, R13.1, U5.17 (O2)
O3: K3.9, R14.1, U5.16 (O3)
